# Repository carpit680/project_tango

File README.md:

# Project Tango source code repository 

## Description:
An autonomous indoor unmanned ground vehicle made from scratch which initially had inspiration from TurtleBot3 but is now different in terms of electronic components, mechanical build as well as software packages.

***

## Workspaces under this repository:
1. ###  control_ws 
    * general purpose motion planning package
2. ### tango_sim_ws
    * Simulation workspace for Project Tnago in various worlds

***

## Usage:
Use the following command to launch Tango in a maze world with RPLidar sensor.

```roslaunch tango_description display.launch```

## Maintainer : _[Arpit Chauhan](https://github.com/carpit680)_

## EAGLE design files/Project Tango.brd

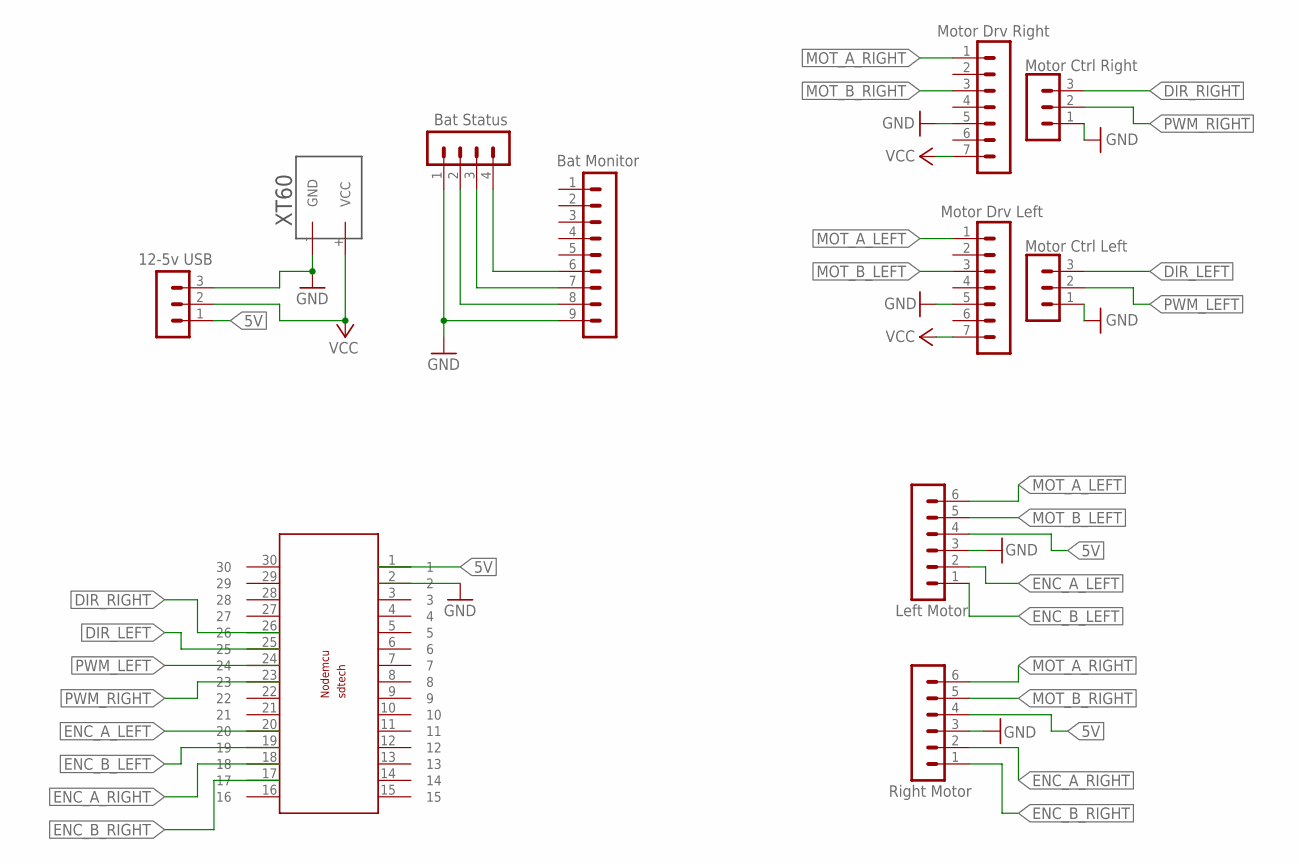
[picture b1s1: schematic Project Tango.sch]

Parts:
BAT_MONITOR: Bat Monitor; MA09-1
BAT_STATUS: Bat Status; MA04-1
LEFTMOTOR: Left Motor; MA06-1
MOTORDRV_RIGHT: Motor Drv Right; MA07-1
SV1: 12-5v USB; MA03-1
SV2: Right Motor; MA06-1
SV3: Motor Drv Left; MA07-1
SV5: Motor Ctrl Right; MA03-1
SV6: Motor Ctrl Left; MA03-1
U$1: Node MCU; NODEMCUESP8266
U$2: XT60

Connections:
5V: LEFTMOTOR.4, SV1.1, SV2.4, U$1.1
DIR_LEFT: SV6.3, U$1.25
DIR_RIGHT: SV5.3, U$1.26
ENC_A_LEFT: LEFTMOTOR.2, U$1.20
ENC_A_RIGHT: SV2.2, U$1.18
ENC_B_LEFT: LEFTMOTOR.1, U$1.19
ENC_B_RIGHT: SV2.1, U$1.17
GND: BAT_MONITOR.9, BAT_STATUS.1, LEFTMOTOR.3, MOTORDRV_RIGHT.5, SV1.3, SV2.3, SV3.5, SV5.1, SV6.1, U$1.2, U$2.- (GND)
MOT_A_LEFT: LEFTMOTOR.6, SV3.1
MOT_A_RIGHT: MOTORDRV_RIGHT.1, SV2.6
MOT_B_LEFT: LEFTMOTOR.5, SV3.3
MOT_B_RIGHT: MOTORDRV_RIGHT.3, SV2.5
unnamed: BAT_MONITOR.8, BAT_STATUS.2
unnamed: BAT_MONITOR.7, BAT_STATUS.3
unnamed: BAT_MONITOR.6, BAT_STATUS.4
PWM_LEFT: SV6.2, U$1.24
PWM_RIGHT: SV5.2, U$1.23
VCC: MOTORDRV_RIGHT.7, SV1.2, SV3.7, U$2.+ (VCC)

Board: 2 copper layers, 11 parts (0 on the bottom side), 18 nets, no tracks yet.

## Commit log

2020-10-15 Added sample arduino code and scrolling text with IP on display.
2020-10-15 added shutdown and restart buttons
2020-10-15 added bash line for restart button
2020-10-20 Added launcher script, log file, and crontab commands
2020-10-21 added messages to shutdown and restart
2020-11-03 added waiting for internet
    Added serial test script and added a wait for internet to connect feature to scrolling display script
2020-11-20 added tango description
    add tango 2.0 description package to the repo
2020-12-07 added gitignore and deleted extra files
2020-12-07 deleted build, devel and logs
2020-12-07 Added wheels to the urdf
2020-12-08 RPLidar added and working
2020-12-08 Readme updated, tango launches in maze world.
2020-12-08 repository re-organization
2020-12-08 deleted pycache folder
2020-12-08 Diff_drive plugin added and tested.
2020-12-08 minor changes
2020-12-10 fixed model joint misalignment
2020-12-10 laser range working
2020-12-10 added teleop script
2020-12-10 modified for windows
2020-12-10 disabled keyboard teleop for windows
2020-12-23 added new obstacle world
2020-12-26 Added cytronMotorDriver libraries
2020-12-26 bare motor control done
2021-01-01 added eagle eda files
2021-01-07 added xacro: tag for noetic
2021-01-08 removed model from obs world
2021-01-08 added urdf file
2021-01-12 dummy link and physics engine step size
2021-01-12 obs.py fixed, lidar pose fixed
2021-01-13 obs.launch included in tango,launch. go to point script added.
2021-01-15 merged control_ws into tango_ws
2021-01-19 added tango.desktop dile
2021-02-28 added 1bhk world commented unnused simulaation settings
2021-03-04 made repo colcon build compatible
2021-03-08 safe distance changed
2021-03-11 python rostest added for obs.py
2021-03-21 dockerfile added
2021-03-23 cosmetic changes in cmake
